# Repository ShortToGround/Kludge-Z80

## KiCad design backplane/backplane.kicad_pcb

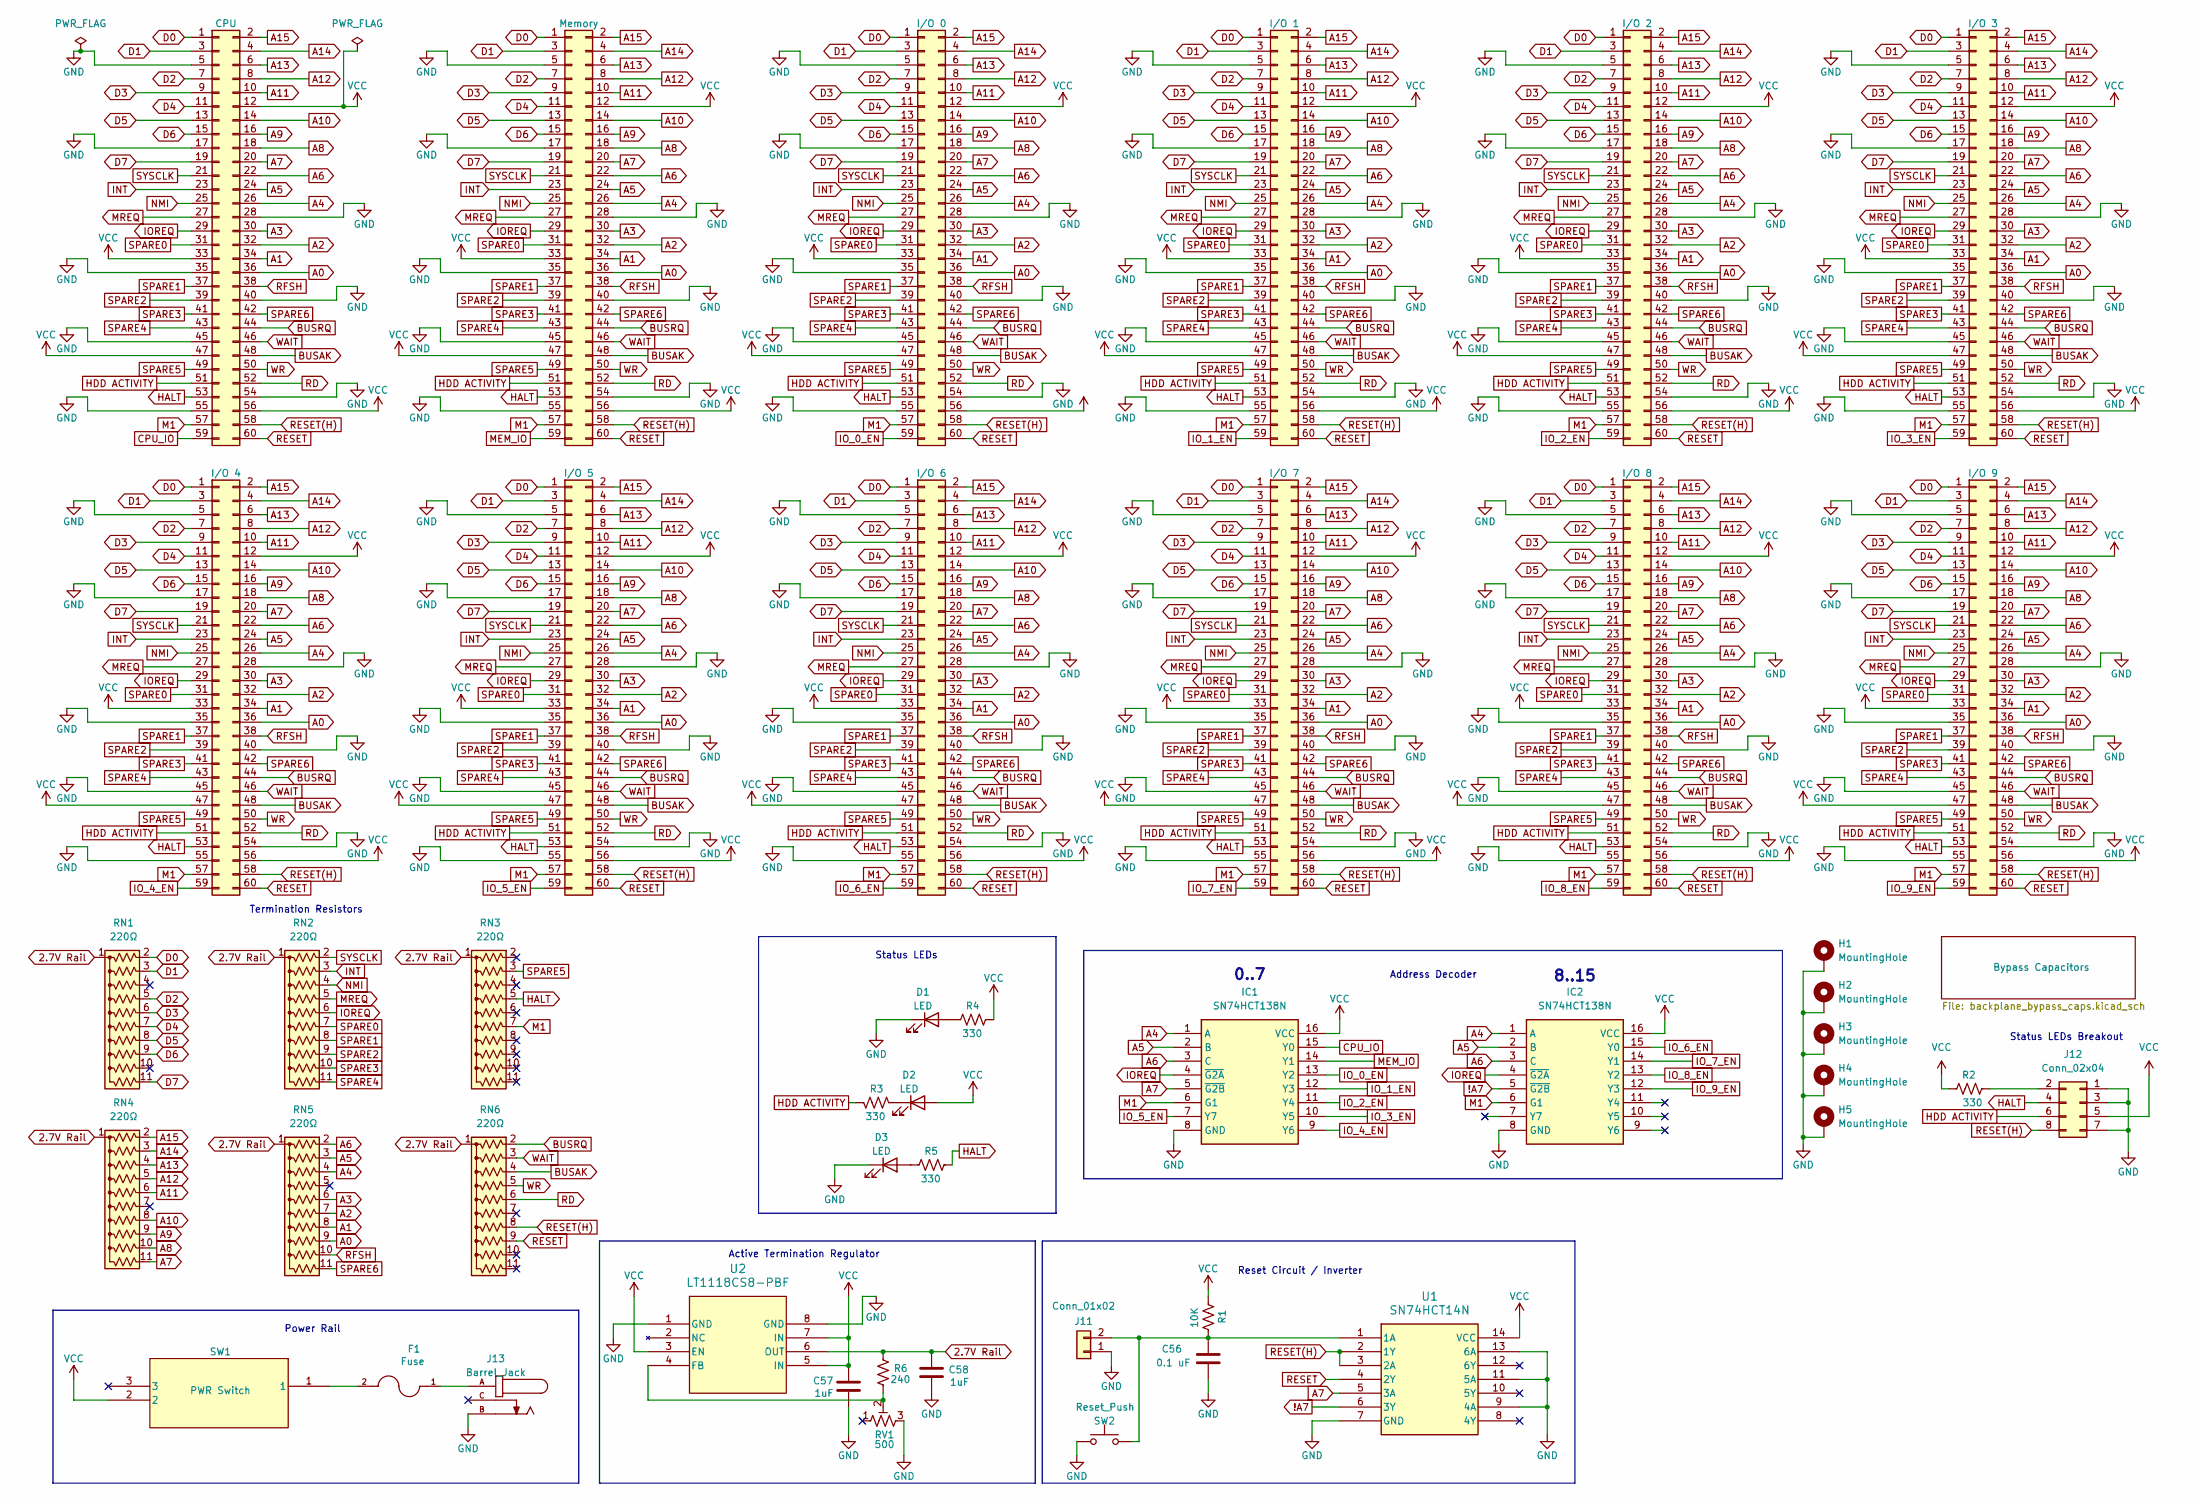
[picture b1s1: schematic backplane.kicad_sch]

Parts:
C56: 0.1 uF; C_Disc_D3.0mm_W1.6mm_P2.50mm
C57, C58: 1uF; C_Disc_D3.0mm_W1.6mm_P2.50mm
D1, D2, D3: LED; LED_D3.0mm
F1: Fuse; FUSE_4628
H1, H2, H3, H4, H5: MountingHole; MountingHole_3.2mm_M3_DIN965_Pad
IC1, IC2: SN74HCT138N; DIP-16_W7.62mm_Socket; Mouser Part Number 595-SN74HCT138N
J1: CPU; PinSocket_2x30_P2.54mm_Vertical
J2: Memory; PinSocket_2x30_P2.54mm_Vertical
J3: I/O 0; PinSocket_2x30_P2.54mm_Vertical
J4: I/O 1; PinSocket_2x30_P2.54mm_Vertical
J5: I/O 2; PinSocket_2x30_P2.54mm_Vertical
J6: I/O 3; PinSocket_2x30_P2.54mm_Vertical
J7: I/O 4; PinSocket_2x30_P2.54mm_Vertical
J8: I/O 5; PinSocket_2x30_P2.54mm_Vertical
J9: I/O 6; PinSocket_2x30_P2.54mm_Vertical
J10: I/O 7; PinSocket_2x30_P2.54mm_Vertical
J11: Conn_01x02; PinHeader_1x02_P2.54mm_Vertical
J12: Conn_02x04; PinHeader_2x04_P2.54mm_Vertical
J13: Barrel_Jack; TENSILITY_54-00129; PARTREV A
J15: I/O 8; PinSocket_2x30_P2.54mm_Vertical
J16: I/O 9; PinSocket_2x30_P2.54mm_Vertical
R1: 10K; R_Axial_DIN0207_L6.3mm_D2.5mm_P10.16mm_Horizontal
R2, R3, R4, R5: 330; R_Axial_DIN0207_L6.3mm_D2.5mm_P10.16mm_Horizontal
R6: 240; R_Axial_DIN0207_L6.3mm_D2.5mm_P10.16mm_Horizontal
RN1, RN2, RN3, RN4, RN5, RN6: 220Ω; R_Array_SIP11
RV1: 500; Potentiometer_Trim_06TR4DA103CP
SW1: PWR Switch; GH36P010001_APM
SW2: Reset_Push; SW_PUSH_6mm
U1: SN74HCT14N; DIP-14_W7.62mm_Socket
U2: LT1118CS8-PBF; LT1118-SO-8_S_LIT

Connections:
2.7V Rail: C58.1, R6.2, RN1.1 (common), RN2.1 (common), RN3.1 (common), RN4.1 (common), RN5.1 (common), RN6.1 (common), U2.6 (OUT)
!A7: IC2.5 (~G2B), U1.6 (3Y)
A0: J1.36, J2.36, J3.36, J4.36, J5.36, J6.36, J7.36, J8.36, J9.36, J10.36, J15.36, J16.36, RN5.9 (R8)
A1: J1.34, J2.34, J3.34, J4.34, J5.34, J6.34, J7.34, J8.34, J9.34, J10.34, J15.34, J16.34, RN5.8 (R7)
A2: J1.32, J2.32, J3.32, J4.32, J5.32, J6.32, J7.32, J8.32, J9.32, J10.32, J15.32, J16.32, RN5.7 (R6)
A3: J1.30, J2.30, J3.30, J4.30, J5.30, J6.30, J7.30, J8.30, J9.30, J10.30, J15.30, J16.30, RN5.6 (R5)
A4: IC1.1 (A), IC2.1 (A), J1.26, J2.26, J3.26, J4.26, J5.26, J6.26, J7.26, J8.26, J9.26, J10.26, J15.26, J16.26, RN5.4 (R3)
A5: IC1.2 (B), IC2.2 (B), J1.24, J2.24, J3.24, J4.24, J5.24, J6.24, J7.24, J8.24, J9.24, J10.24, J15.24, J16.24, RN5.3 (R2)
A6: IC1.3 (C), IC2.3 (C), J1.22, J2.22, J3.22, J4.22, J5.22, J6.22, J7.22, J8.22, J9.22, J10.22, J15.22, J16.22, RN5.2 (R1)
A7: IC1.5 (~G2B), J1.20, J2.20, J3.20, J4.20, J5.20, J6.20, J7.20, J8.20, J9.20, J10.20, J15.20, J16.20, RN4.11 (R10), U1.5 (3A)
A8: J1.18, J2.18, J3.18, J4.18, J5.18, J6.18, J7.18, J8.18, J9.18, J10.18, J15.18, J16.18, RN4.10 (R9)
A9: J1.16, J2.16, J3.16, J4.16, J5.16, J6.16, J7.16, J8.16, J9.16, J10.16, J15.16, J16.16, RN4.9 (R8)
A10: J1.14, J2.14, J3.14, J4.14, J5.14, J6.14, J7.14, J8.14, J9.14, J10.14, J15.14, J16.14, RN4.8 (R7)
A11: J1.10, J2.10, J3.10, J4.10, J5.10, J6.10, J7.10, J8.10, J9.10, J10.10, J15.10, J16.10, RN4.6 (R5)
A12: J1.8, J2.8, J3.8, J4.8, J5.8, J6.8, J7.8, J8.8, J9.8, J10.8, J15.8, J16.8, RN4.5 (R4)
A13: J1.6, J2.6, J3.6, J4.6, J5.6, J6.6, J7.6, J8.6, J9.6, J10.6, J15.6, J16.6, RN4.4 (R3)
A14: J1.4, J2.4, J3.4, J4.4, J5.4, J6.4, J7.4, J8.4, J9.4, J10.4, J15.4, J16.4, RN4.3 (R2)
A15: J1.2, J2.2, J3.2, J4.2, J5.2, J6.2, J7.2, J8.2, J9.2, J10.2, J15.2, J16.2, RN4.2 (R1)
BUSAK: J1.48, J2.48, J3.48, J4.48, J5.48, J6.48, J7.48, J8.48, J9.48, J10.48, J15.48, J16.48, RN6.4 (R3)
BUSRQ: J1.44, J2.44, J3.44, J4.44, J5.44, J6.44, J7.44, J8.44, J9.44, J10.44, J15.44, J16.44, RN6.2 (R1)
CPU_IO: IC1.15 (Y0), J1.59
D0: J1.1, J2.1, J3.1, J4.1, J5.1, J6.1, J7.1, J8.1, J9.1, J10.1, J15.1, J16.1, RN1.2 (R1)
D1: J1.3, J2.3, J3.3, J4.3, J5.3, J6.3, J7.3, J8.3, J9.3, J10.3, J15.3, J16.3, RN1.3 (R2)
D2: J1.7, J2.7, J3.7, J4.7, J5.7, J6.7, J7.7, J8.7, J9.7, J10.7, J15.7, J16.7, RN1.5 (R4)
D3: J1.9, J2.9, J3.9, J4.9, J5.9, J6.9, J7.9, J8.9, J9.9, J10.9, J15.9, J16.9, RN1.6 (R5)
D4: J1.11, J2.11, J3.11, J4.11, J5.11, J6.11, J7.11, J8.11, J9.11, J10.11, J15.11, J16.11, RN1.7 (R6)
D5: J1.13, J2.13, J3.13, J4.13, J5.13, J6.13, J7.13, J8.13, J9.13, J10.13, J15.13, J16.13, RN1.8 (R7)
D6: J1.15, J2.15, J3.15, J4.15, J5.15, J6.15, J7.15, J8.15, J9.15, J10.15, J15.15, J16.15, RN1.9 (R8)
D7: J1.19, J2.19, J3.19, J4.19, J5.19, J6.19, J7.19, J8.19, J9.19, J10.19, J15.19, J16.19, RN1.11 (R10)
GND: C56.2, C57.2, C58.2, D1.1 (K), D3.1 (K), H1.1, H2.1, H3.1, H4.1, H5.1, IC1.8 (GND), IC2.8 (GND), J1.5, J1.17, J1.28, J1.35, J1.40, J1.45, J1.54, J1.55, J2.5, J2.17, J2.28, J2.35, J2.40, J2.45, J2.54, J2.55, J3.5, J3.17, J3.28, J3.35, J3.40, J3.45, J3.54, J3.55, J4.5, J4.17, J4.28, J4.35, J4.40, J4.45, J4.54, J4.55, J5.5, J5.17, J5.28, J5.35, J5.40, J5.45, J5.54, J5.55, J6.5, J6.17, J6.28, J6.35, J6.40, J6.45, J6.54, J6.55, J7.5, J7.17, J7.28, J7.35, J7.40, J7.45, J7.54, J7.55, J8.5, J8.17, J8.28, J8.35, J8.40, J8.45, J8.54, J8.55, J9.5, J9.17, J9.28, J9.35, J9.40, J9.45, J9.54, J9.55, J10.5, J10.17, J10.28, J10.35, J10.40, J10.45, J10.54, J10.55, J11.1, J12.1, J12.3, J12.7, J13.B, J15.5, J15.17, J15.28, J15.35, J15.40, J15.45, J15.54, J15.55, J16.5, J16.17, J16.28, J16.35, J16.40, J16.45, J16.54, J16.55, RV1.3, SW2.1, U1.7 (GND), U1.9 (4A), U1.11 (5A), U1.13 (6A), U2.1 (GND), U2.8 (GND); also elsewhere on the board
HALT: J1.53, J2.53, J3.53, J4.53, J5.53, J6.53, J7.53, J8.53, J9.53, J10.53, J12.4, J15.53, J16.53, R5.2, RN3.5 (R4)
HDD ACTIVITY: J1.51, J2.51, J3.51, J4.51, J5.51, J6.51, J7.51, J8.51, J9.51, J10.51, J12.6, J15.51, J16.51, R3.2
INT: J1.23, J2.23, J3.23, J4.23, J5.23, J6.23, J7.23, J8.23, J9.23, J10.23, J15.23, J16.23, RN2.3 (R2)
IOREQ: IC1.4 (~G2A), IC2.4 (~G2A), J1.29, J2.29, J3.29, J4.29, J5.29, J6.29, J7.29, J8.29, J9.29, J10.29, J15.29, J16.29, RN2.6 (R5)
IO_0_EN: IC1.13 (Y2), J3.59
IO_1_EN: IC1.12 (Y3), J4.59
IO_2_EN: IC1.11 (Y4), J5.59
IO_3_EN: IC1.10 (Y5), J6.59
IO_4_EN: IC1.9 (Y6), J7.59
IO_5_EN: IC1.7 (Y7), J8.59
IO_6_EN: IC2.15 (Y0), J9.59
IO_7_EN: IC2.14 (Y1), J10.59
IO_8_EN: IC2.13 (Y2), J15.59
IO_9_EN: IC2.12 (Y3), J16.59
M1: IC1.6 (G1), IC2.6 (G1), J1.57, J2.57, J3.57, J4.57, J5.57, J6.57, J7.57, J8.57, J9.57, J10.57, J15.57, J16.57, RN3.7 (R6)
MEM_IO: IC1.14 (Y1), J2.59
MREQ: J1.27, J2.27, J3.27, J4.27, J5.27, J6.27, J7.27, J8.27, J9.27, J10.27, J15.27, J16.27, RN2.5 (R4)
NMI: J1.25, J2.25, J3.25, J4.25, J5.25, J6.25, J7.25, J8.25, J9.25, J10.25, J15.25, J16.25, RN2.4 (R3)
unnamed: D1.2 (A), R4.1
unnamed: D2.1 (K), R3.1
unnamed: D3.2 (A), R5.1
unnamed: F1.1, J13.A
unnamed: F1.2, SW1.1
unnamed: C56.1, J11.2, R1.2, SW2.2, U1.1 (1A)
unnamed: J12.2, R2.2
unnamed: R6.1, RV1.2, U2.4 (FB)
RD: J1.52, J2.52, J3.52, J4.52, J5.52, J6.52, J7.52, J8.52, J9.52, J10.52, J15.52, J16.52, RN6.6 (R5)
RESET: J1.60, J2.60, J3.60, J4.60, J5.60, J6.60, J7.60, J8.60, J9.60, J10.60, J15.60, J16.60, RN6.9 (R8), U1.4 (2Y)
RESET(H): J1.58, J2.58, J3.58, J4.58, J5.58, J6.58, J7.58, J8.58, J9.58, J10.58, J12.8, J15.58, J16.58, RN6.8 (R7), U1.2 (1Y), U1.3 (2A)
RFSH: J1.38, J2.38, J3.38, J4.38, J5.38, J6.38, J7.38, J8.38, J9.38, J10.38, J15.38, J16.38, RN5.10 (R9)
SPARE0: J1.31, J2.31, J3.31, J4.31, J5.31, J6.31, J7.31, J8.31, J9.31, J10.31, J15.31, J16.31, RN2.7 (R6)
SPARE1: J1.37, J2.37, J3.37, J4.37, J5.37, J6.37, J7.37, J8.37, J9.37, J10.37, J15.37, J16.37, RN2.8 (R7)
SPARE2: J1.39, J2.39, J3.39, J4.39, J5.39, J6.39, J7.39, J8.39, J9.39, J10.39, J15.39, J16.39, RN2.9 (R8)
SPARE3: J1.41, J2.41, J3.41, J4.41, J5.41, J6.41, J7.41, J8.41, J9.41, J10.41, J15.41, J16.41, RN2.10 (R9)
SPARE4: J1.43, J2.43, J3.43, J4.43, J5.43, J6.43, J7.43, J8.43, J9.43, J10.43, J15.43, J16.43, RN2.11 (R10)
SPARE5: J1.49, J2.49, J3.49, J4.49, J5.49, J6.49, J7.49, J8.49, J9.49, J10.49, J15.49, J16.49, RN3.3 (R2)
SPARE6: J1.42, J2.42, J3.42, J4.42, J5.42, J6.42, J7.42, J8.42, J9.42, J10.42, J15.42, J16.42, RN5.11 (R10)
SYSCLK: J1.21, J2.21, J3.21, J4.21, J5.21, J6.21, J7.21, J8.21, J9.21, J10.21, J15.21, J16.21, RN2.2 (R1)
VCC: C57.1, D2.2 (A), IC1.16 (VCC), IC2.16 (VCC), J1.12, J1.33, J1.47, J1.56, J2.12, J2.33, J2.47, J2.56, J3.12, J3.33, J3.47, J3.56, J4.12, J4.33, J4.47, J4.56, J5.12, J5.33, J5.47, J5.56, J6.12, J6.33, J6.47, J6.56, J7.12, J7.33, J7.47, J7.56, J8.12, J8.33, J8.47, J8.56, J9.12, J9.33, J9.47, J9.56, J10.12, J10.33, J10.47, J10.56, J12.5, J15.12, J15.33, J15.47, J15.56, J16.12, J16.33, J16.47, J16.56, R1.1, R2.1, R4.2, SW1.2, U1.14 (VCC), U2.3 (EN), U2.5 (IN), U2.7 (IN); also elsewhere on the board
WAIT: J1.46, J2.46, J3.46, J4.46, J5.46, J6.46, J7.46, J8.46, J9.46, J10.46, J15.46, J16.46, RN6.3 (R2)
WR: J1.50, J2.50, J3.50, J4.50, J5.50, J6.50, J7.50, J8.50, J9.50, J10.50, J15.50, J16.50, RN6.5 (R4)

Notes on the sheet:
Address Decoder
Status LEDs
Termination Resistors
Active Termination Regulator
Power Rail
Status LEDs Breakout
8..15
Reset Circuit / Inverter
0..7

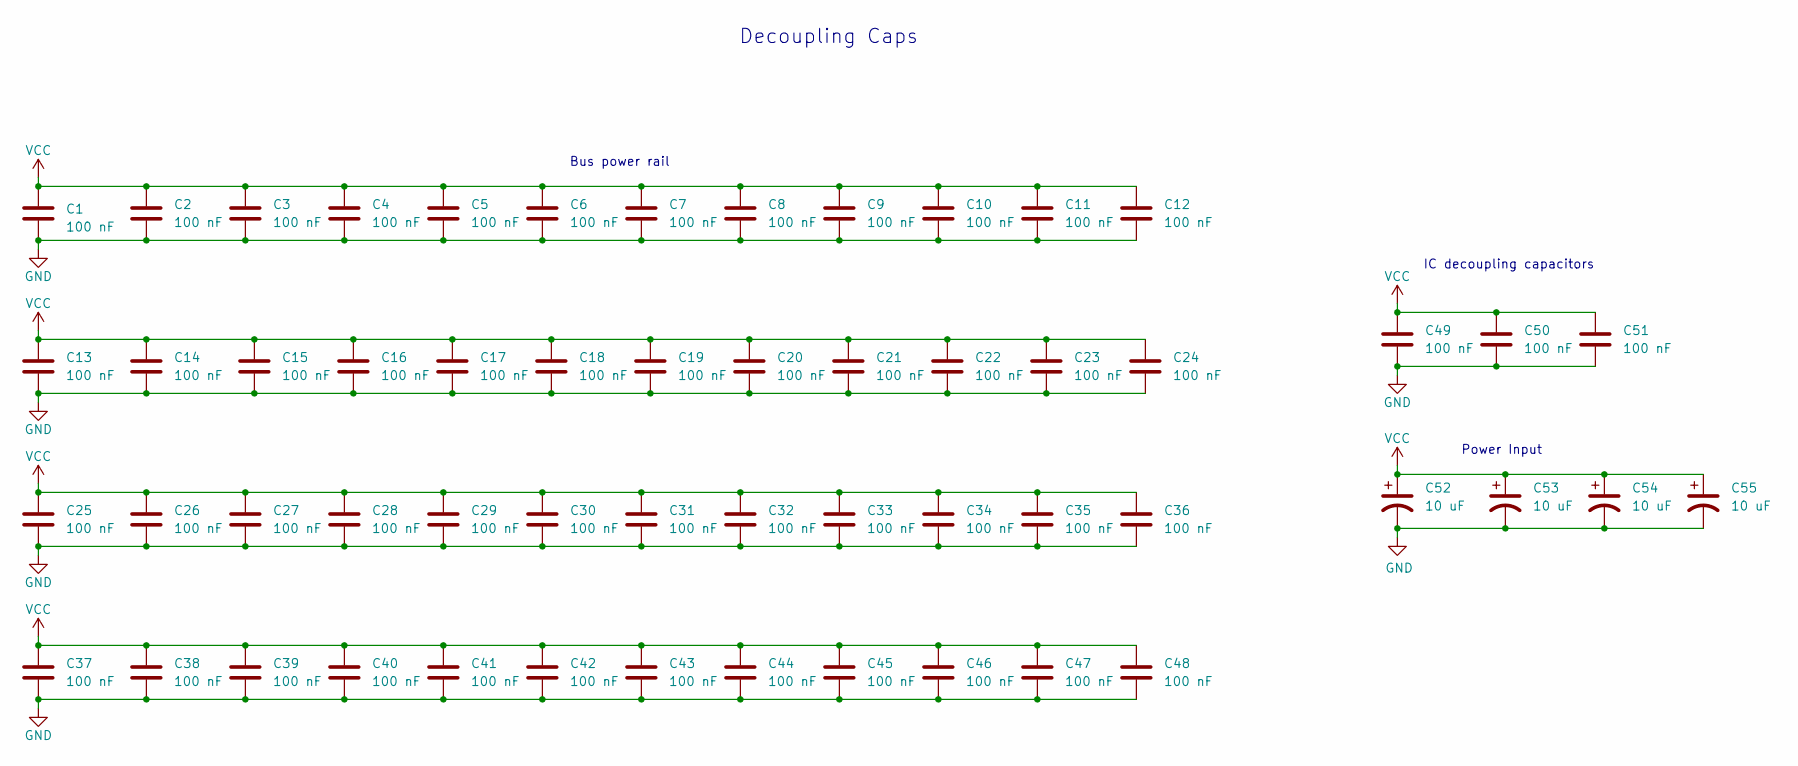
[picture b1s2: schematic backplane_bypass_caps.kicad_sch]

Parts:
C1, C2, C3, C4, C5, C6, C7, C8, C9, C10, C11, C12, C13, C14, C15, C16, C17, C18, C19, C20, C21, C22, C23, C24, C25, C26, C27, C28, C29, C30, C31, C32, C33, C34, C35, C36, C37, C38, C39, C40, C41, C42, C43, C44, C45, C46, C47, C48, C49, C50, C51: 100 nF; C_Disc_D3.0mm_W1.6mm_P2.50mm
C52, C53, C54, C55: 10 uF; C_Radial_D6.3mm_H7.0mm_P2.50mm

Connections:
GND: C1.2, C2.2, C3.2, C4.2, C5.2, C6.2, C7.2, C8.2, C9.2, C10.2, C11.2, C12.2, C13.2, C14.2, C15.2, C16.2, C17.2, C18.2, C19.2, C20.2, C21.2, C22.2, C23.2, C24.2, C25.2, C26.2, C27.2, C28.2, C29.2, C30.2, C31.2, C32.2, C33.2, C34.2, C35.2, C36.2, C37.2, C38.2, C39.2, C40.2, C41.2, C42.2, C43.2, C44.2, C45.2, C46.2, C47.2, C48.2, C49.2, C50.2, C51.2, C52.2, C53.2, C54.2, C55.2; also elsewhere on the board
VCC: C1.1, C2.1, C3.1, C4.1, C5.1, C6.1, C7.1, C8.1, C9.1, C10.1, C11.1, C12.1, C13.1, C14.1, C15.1, C16.1, C17.1, C18.1, C19.1, C20.1, C21.1, C22.1, C23.1, C24.1, C25.1, C26.1, C27.1, C28.1, C29.1, C30.1, C31.1, C32.1, C33.1, C34.1, C35.1, C36.1, C37.1, C38.1, C39.1, C40.1, C41.1, C42.1, C43.1, C44.1, C45.1, C46.1, C47.1, C48.1, C49.1, C50.1, C51.1, C52.1, C53.1, C54.1, C55.1; also elsewhere on the board

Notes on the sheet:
Power Input
IC decoupling capacitors
Bus power rail
Decoupling Caps

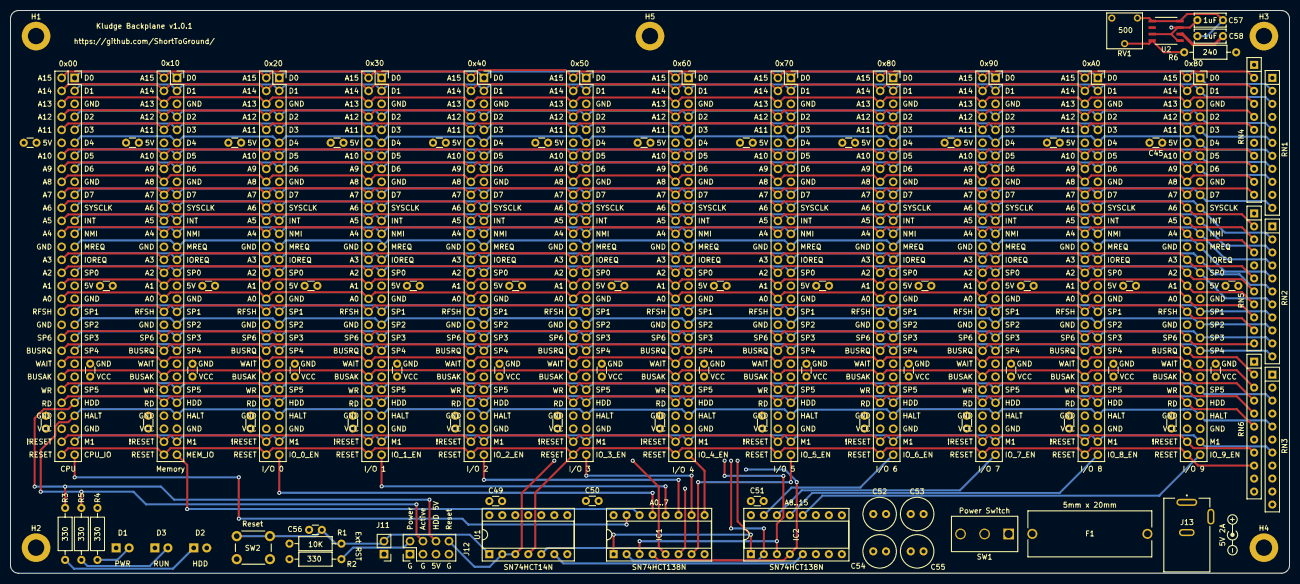
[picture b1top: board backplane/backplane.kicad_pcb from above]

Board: 4 copper layers, 250.0 x 110.0 mm, 101 parts (0 on the bottom side), 71 nets.

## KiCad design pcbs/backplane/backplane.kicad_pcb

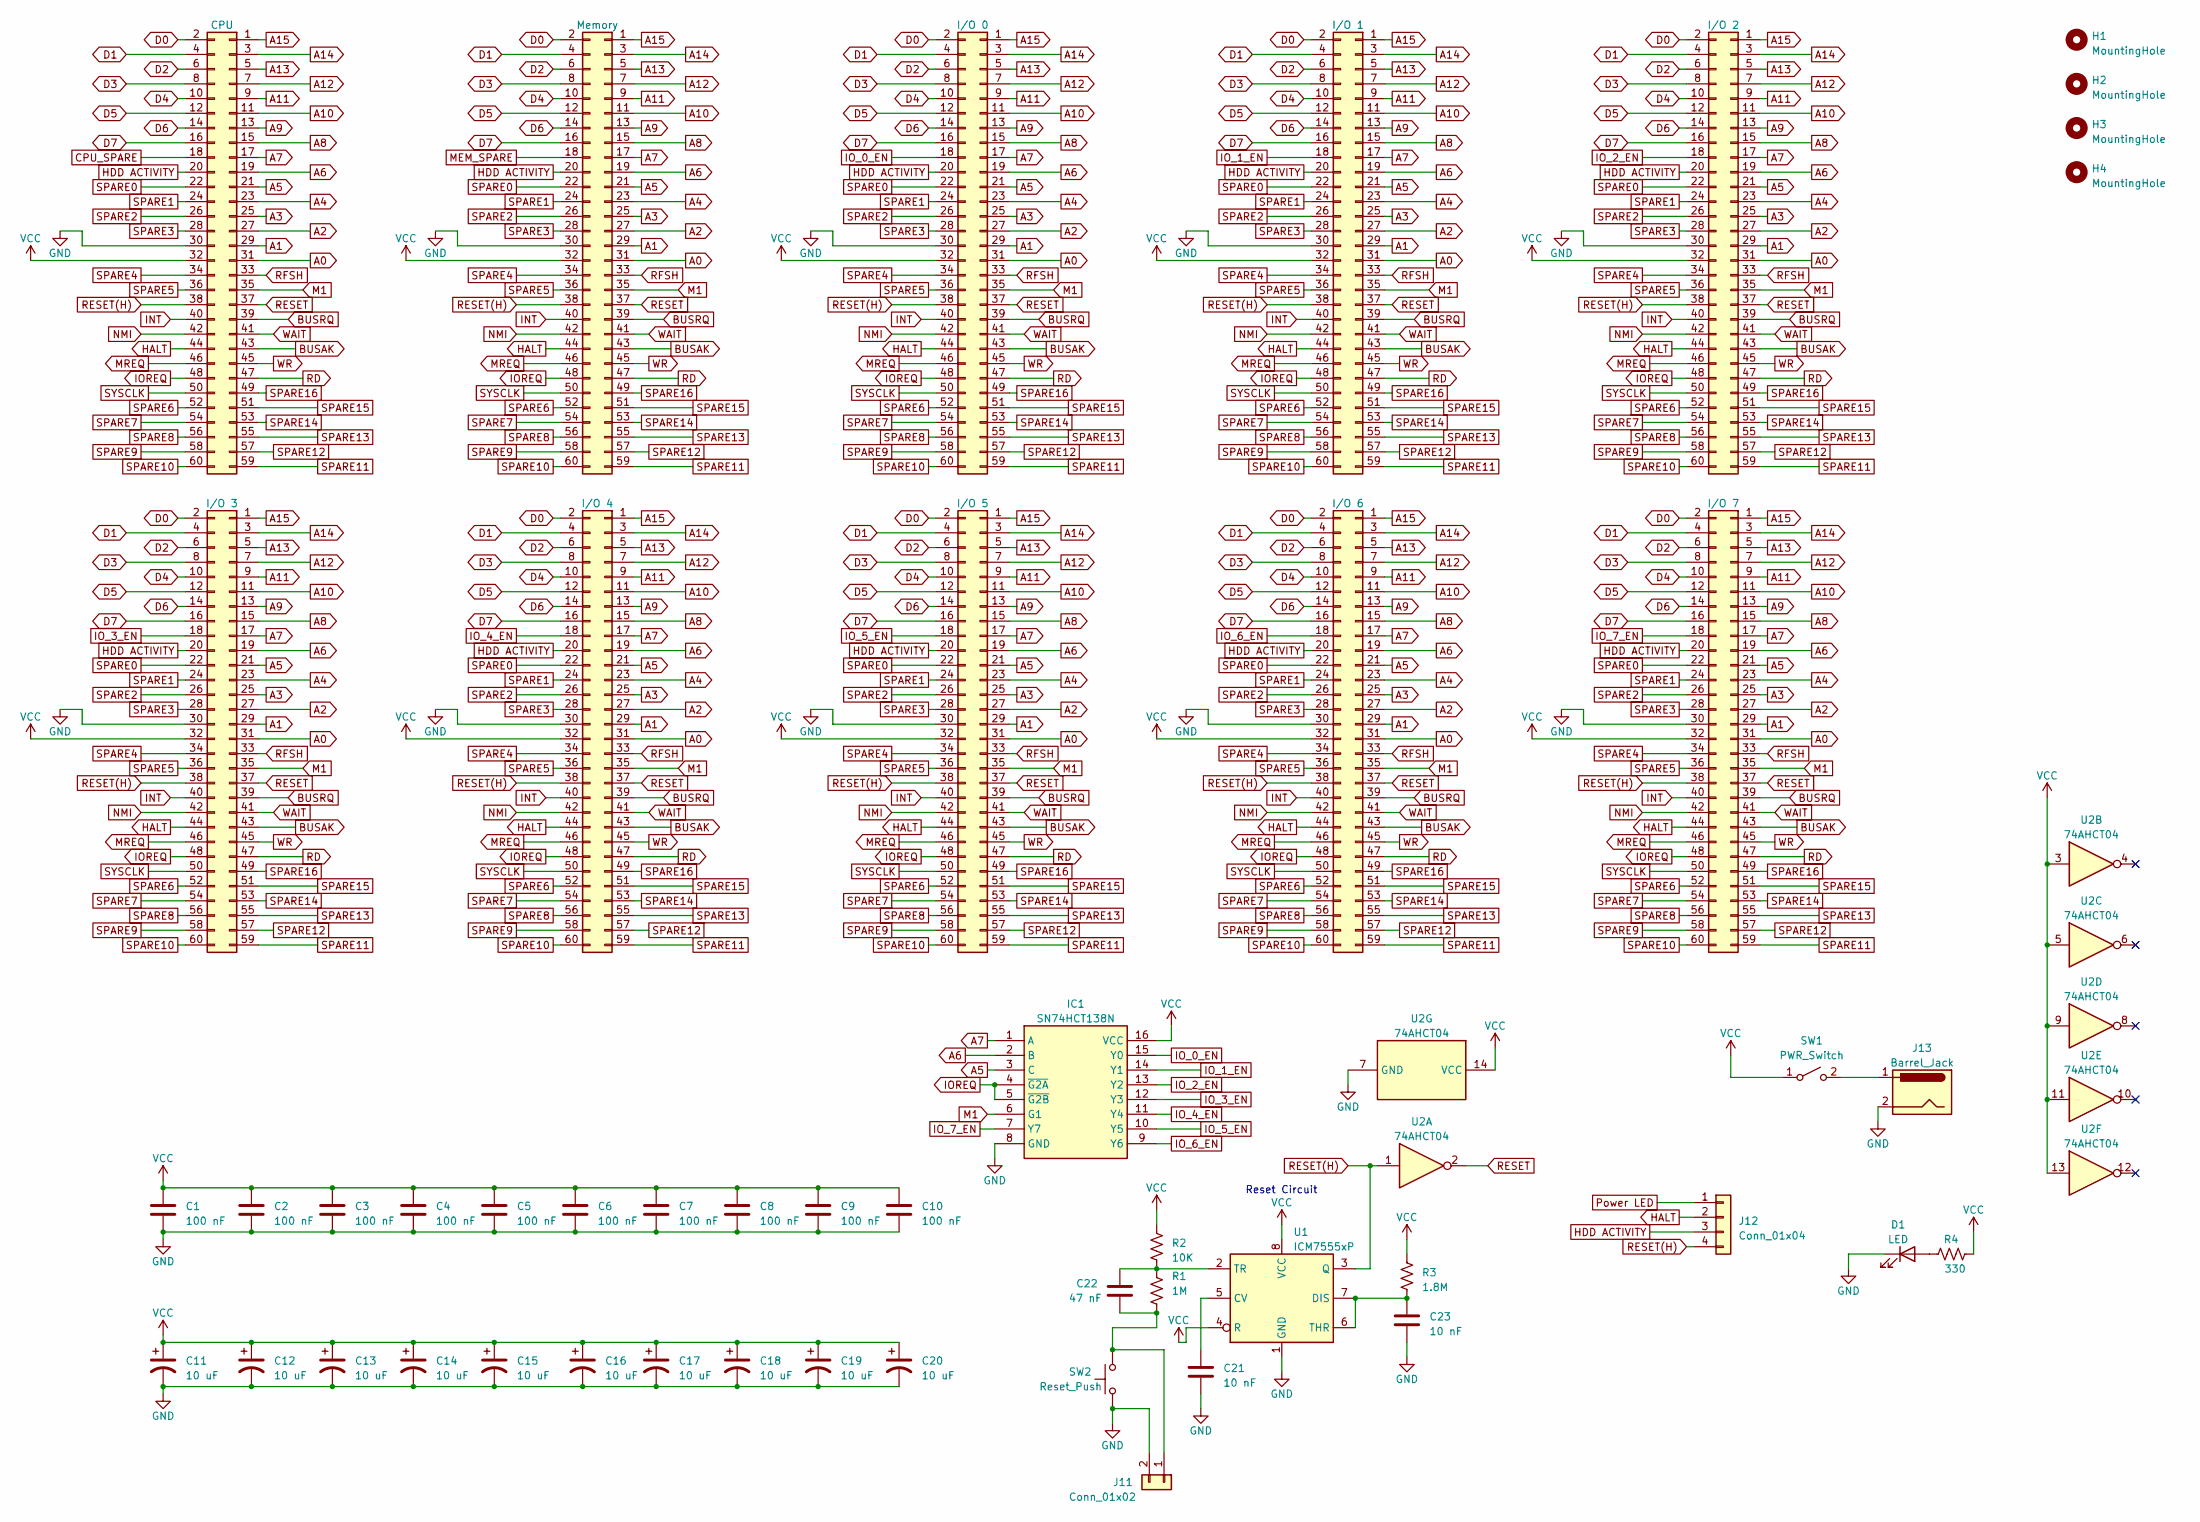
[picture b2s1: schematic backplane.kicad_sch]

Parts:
C1, C2, C3, C4, C5, C6, C7, C8, C9, C10: 100 nF; C_Disc_D3.0mm_W1.6mm_P2.50mm
C11, C12, C13, C14, C15, C16, C17, C18, C19, C20: 10 uF; C_Radial_D6.3mm_H7.0mm_P2.50mm
C21, C23: 10 nF; C_Disc_D3.0mm_W1.6mm_P2.50mm
C22: 47 nF; C_Disc_D3.0mm_W1.6mm_P2.50mm
D1: LED; LED_D3.0mm
H1, H2, H3, H4: MountingHole; MountingHole_3.2mm_M3
IC1: SN74HCT138N; Mouser Part Number 595-SN74HCT138N
J1: CPU; PinSocket_2x30_P2.54mm_Vertical
J2: Memory; PinSocket_2x30_P2.54mm_Vertical
J3: I/O 0; PinSocket_2x30_P2.54mm_Vertical
J4: I/O 1; PinSocket_2x30_P2.54mm_Vertical
J5: I/O 2; PinSocket_2x30_P2.54mm_Vertical
J6: I/O 3; PinSocket_2x30_P2.54mm_Vertical
J7: I/O 4; PinSocket_2x30_P2.54mm_Vertical
J8: I/O 5; PinSocket_2x30_P2.54mm_Vertical
J9: I/O 6; PinSocket_2x30_P2.54mm_Vertical
J10: I/O 7; PinSocket_2x30_P2.54mm_Vertical
J11: Conn_01x02; PinHeader_1x02_P2.54mm_Vertical
J12: Conn_01x04; PinHeader_1x04_P2.54mm_Vertical
J13: Barrel_Jack; BarrelJack_Horizontal
R1: 1M; R_Axial_DIN0204_L3.6mm_D1.6mm_P5.08mm_Horizontal
R2: 10K; R_Axial_DIN0204_L3.6mm_D1.6mm_P5.08mm_Horizontal
R3: 1.8M; R_Axial_DIN0204_L3.6mm_D1.6mm_P5.08mm_Horizontal
R4: 330; R_Axial_DIN0204_L3.6mm_D1.6mm_P5.08mm_Horizontal
SW1: PWR_Switch; SW_DIP_SPSTx01_Slide_9.78x4.72mm_W7.62mm_P2.54mm
SW2: Reset_Push; SW_PUSH_6mm
U1: ICM7555xP; DIP-8_W7.62mm
U2: 74AHCT04; DIP-14_W7.62mm

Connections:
A0: J1.31, J2.31, J3.31, J4.31, J5.31, J6.31, J7.31, J8.31, J9.31, J10.31
A1: J1.29, J2.29, J3.29, J4.29, J5.29, J6.29, J7.29, J8.29, J9.29, J10.29
A2: J1.27, J2.27, J3.27, J4.27, J5.27, J6.27, J7.27, J8.27, J9.27, J10.27
A3: J1.25, J2.25, J3.25, J4.25, J5.25, J6.25, J7.25, J8.25, J9.25, J10.25
A4: J1.23, J2.23, J3.23, J4.23, J5.23, J6.23, J7.23, J8.23, J9.23, J10.23
A5: IC1.3 (C), J1.21, J2.21, J3.21, J4.21, J5.21, J6.21, J7.21, J8.21, J9.21, J10.21
A6: IC1.2 (B), J1.19, J2.19, J3.19, J4.19, J5.19, J6.19, J7.19, J8.19, J9.19, J10.19
A7: IC1.1 (A), J1.17, J2.17, J3.17, J4.17, J5.17, J6.17, J7.17, J8.17, J9.17, J10.17
A8: J1.15, J2.15, J3.15, J4.15, J5.15, J6.15, J7.15, J8.15, J9.15, J10.15
A9: J1.13, J2.13, J3.13, J4.13, J5.13, J6.13, J7.13, J8.13, J9.13, J10.13
A10: J1.11, J2.11, J3.11, J4.11, J5.11, J6.11, J7.11, J8.11, J9.11, J10.11
A11: J1.9, J2.9, J3.9, J4.9, J5.9, J6.9, J7.9, J8.9, J9.9, J10.9
A12: J1.7, J2.7, J3.7, J4.7, J5.7, J6.7, J7.7, J8.7, J9.7, J10.7
A13: J1.5, J2.5, J3.5, J4.5, J5.5, J6.5, J7.5, J8.5, J9.5, J10.5
A14: J1.3, J2.3, J3.3, J4.3, J5.3, J6.3, J7.3, J8.3, J9.3, J10.3
A15: J1.1, J2.1, J3.1, J4.1, J5.1, J6.1, J7.1, J8.1, J9.1, J10.1
BUSAK: J1.43, J2.43, J3.43, J4.43, J5.43, J6.43, J7.43, J8.43, J9.43, J10.43
BUSRQ: J1.39, J2.39, J3.39, J4.39, J5.39, J6.39, J7.39, J8.39, J9.39, J10.39
CPU_SPARE: J1.18
D0: J1.2, J2.2, J3.2, J4.2, J5.2, J6.2, J7.2, J8.2, J9.2, J10.2
D1: J1.4, J2.4, J3.4, J4.4, J5.4, J6.4, J7.4, J8.4, J9.4, J10.4
D2: J1.6, J2.6, J3.6, J4.6, J5.6, J6.6, J7.6, J8.6, J9.6, J10.6
D3: J1.8, J2.8, J3.8, J4.8, J5.8, J6.8, J7.8, J8.8, J9.8, J10.8
D4: J1.10, J2.10, J3.10, J4.10, J5.10, J6.10, J7.10, J8.10, J9.10, J10.10
D5: J1.12, J2.12, J3.12, J4.12, J5.12, J6.12, J7.12, J8.12, J9.12, J10.12
D6: J1.14, J2.14, J3.14, J4.14, J5.14, J6.14, J7.14, J8.14, J9.14, J10.14
D7: J1.16, J2.16, J3.16, J4.16, J5.16, J6.16, J7.16, J8.16, J9.16, J10.16
GND: C1.2, C2.2, C3.2, C4.2, C5.2, C6.2, C7.2, C8.2, C9.2, C10.2, C11.2, C12.2, C13.2, C14.2, C15.2, C16.2, C17.2, C18.2, C19.2, C20.2, C21.2, C23.2, D1.1 (K), IC1.8 (GND), J1.30, J2.30, J3.30, J4.30, J5.30, J6.30, J7.30, J8.30, J9.30, J10.30, J11.2, J13.2, SW2.1, U1.1 (GND), U2.7 (GND)
HALT: J1.44, J2.44, J3.44, J4.44, J5.44, J6.44, J7.44, J8.44, J9.44, J10.44, J12.2
HDD ACTIVITY: J1.20, J2.20, J3.20, J4.20, J5.20, J6.20, J7.20, J8.20, J9.20, J10.20, J12.3
INT: J1.40, J2.40, J3.40, J4.40, J5.40, J6.40, J7.40, J8.40, J9.40, J10.40
IOREQ: IC1.4 (~G2A), IC1.5 (~G2B), J1.48, J2.48, J3.48, J4.48, J5.48, J6.48, J7.48, J8.48, J9.48, J10.48
IO_0_EN: IC1.15 (Y0), J3.18
IO_1_EN: IC1.14 (Y1), J4.18
IO_2_EN: IC1.13 (Y2), J5.18
IO_3_EN: IC1.12 (Y3), J6.18
IO_4_EN: IC1.11 (Y4), J7.18
IO_5_EN: IC1.10 (Y5), J8.18
IO_6_EN: IC1.9 (Y6), J9.18
IO_7_EN: IC1.7 (Y7), J10.18
M1: IC1.6 (G1), J1.35, J2.35, J3.35, J4.35, J5.35, J6.35, J7.35, J8.35, J9.35, J10.35
MEM_SPARE: J2.18
MREQ: J1.46, J2.46, J3.46, J4.46, J5.46, J6.46, J7.46, J8.46, J9.46, J10.46
NMI: J1.42, J2.42, J3.42, J4.42, J5.42, J6.42, J7.42, J8.42, J9.42, J10.42
unnamed: D1.2 (A), R4.1
unnamed: C22.2, J11.1, R1.2, SW2.2
unnamed: J13.1, SW1.2 (B)
unnamed: C21.1, U1.5 (CV)
unnamed: C23.1, R3.2, U1.6 (THR), U1.7 (DIS)
unnamed: C22.1, R1.1, R2.2, U1.2 (TR)
Power LED: J12.1
RD: J1.47, J2.47, J3.47, J4.47, J5.47, J6.47, J7.47, J8.47, J9.47, J10.47
RESET: J1.37, J2.37, J3.37, J4.37, J5.37, J6.37, J7.37, J8.37, J9.37, J10.37, U2.2
RESET(H): J1.38, J2.38, J3.38, J4.38, J5.38, J6.38, J7.38, J8.38, J9.38, J10.38, J12.4, U1.3 (Q), U2.1
RFSH: J1.33, J2.33, J3.33, J4.33, J5.33, J6.33, J7.33, J8.33, J9.33, J10.33
SPARE0: J1.22, J2.22, J3.22, J4.22, J5.22, J6.22, J7.22, J8.22, J9.22, J10.22
SPARE1: J1.24, J2.24, J3.24, J4.24, J5.24, J6.24, J7.24, J8.24, J9.24, J10.24
SPARE2: J1.26, J2.26, J3.26, J4.26, J5.26, J6.26, J7.26, J8.26, J9.26, J10.26
SPARE3: J1.28, J2.28, J3.28, J4.28, J5.28, J6.28, J7.28, J8.28, J9.28, J10.28
SPARE4: J1.34, J2.34, J3.34, J4.34, J5.34, J6.34, J7.34, J8.34, J9.34, J10.34
SPARE5: J1.36, J2.36, J3.36, J4.36, J5.36, J6.36, J7.36, J8.36, J9.36, J10.36
SPARE6: J1.52, J2.52, J3.52, J4.52, J5.52, J6.52, J7.52, J8.52, J9.52, J10.52
SPARE7: J1.54, J2.54, J3.54, J4.54, J5.54, J6.54, J7.54, J8.54, J9.54, J10.54
SPARE8: J1.56, J2.56, J3.56, J4.56, J5.56, J6.56, J7.56, J8.56, J9.56, J10.56
SPARE9: J1.58, J2.58, J3.58, J4.58, J5.58, J6.58, J7.58, J8.58, J9.58, J10.58
SPARE10: J1.60, J2.60, J3.60, J4.60, J5.60, J6.60, J7.60, J8.60, J9.60, J10.60
SPARE11: J1.59, J2.59, J3.59, J4.59, J5.59, J6.59, J7.59, J8.59, J9.59, J10.59
SPARE12: J1.57, J2.57, J3.57, J4.57, J5.57, J6.57, J7.57, J8.57, J9.57, J10.57
SPARE13: J1.55, J2.55, J3.55, J4.55, J5.55, J6.55, J7.55, J8.55, J9.55, J10.55
SPARE14: J1.53, J2.53, J3.53, J4.53, J5.53, J6.53, J7.53, J8.53, J9.53, J10.53
SPARE15: J1.51, J2.51, J3.51, J4.51, J5.51, J6.51, J7.51, J8.51, J9.51, J10.51
SPARE16: J1.49, J2.49, J3.49, J4.49, J5.49, J6.49, J7.49, J8.49, J9.49, J10.49
SYSCLK: J1.50, J2.50, J3.50, J4.50, J5.50, J6.50, J7.50, J8.50, J9.50, J10.50
VCC: C1.1, C2.1, C3.1, C4.1, C5.1, C6.1, C7.1, C8.1, C9.1, C10.1, C11.1, C12.1, C13.1, C14.1, C15.1, C16.1, C17.1, C18.1, C19.1, C20.1, IC1.16 (VCC), J1.32, J2.32, J3.32, J4.32, J5.32, J6.32, J7.32, J8.32, J9.32, J10.32, R2.1, R3.1, R4.2, SW1.1 (A), U1.4 (R), U1.8 (VCC), U2.3, U2.5, U2.9, U2.11, U2.13, U2.14 (VCC)
WAIT: J1.41, J2.41, J3.41, J4.41, J5.41, J6.41, J7.41, J8.41, J9.41, J10.41
WR: J1.45, J2.45, J3.45, J4.45, J5.45, J6.45, J7.45, J8.45, J9.45, J10.45

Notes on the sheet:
Reset Circuit

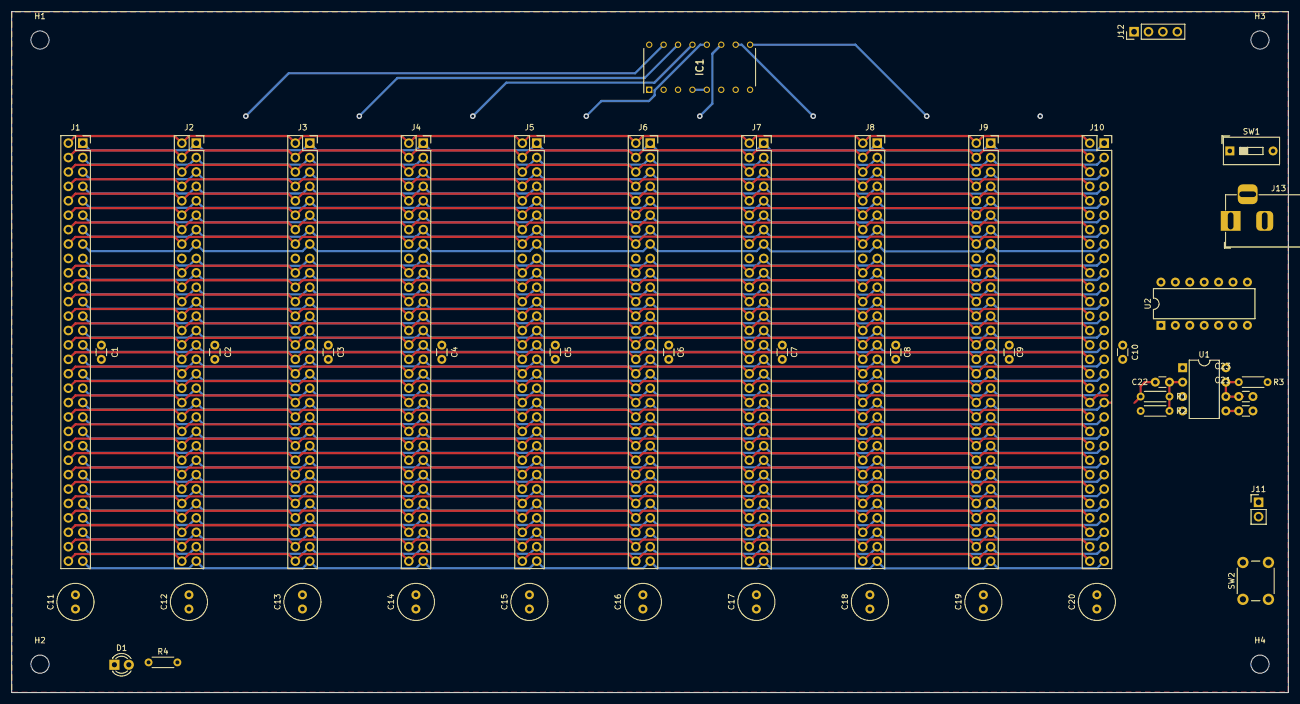
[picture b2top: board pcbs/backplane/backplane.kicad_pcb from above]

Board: 4 copper layers, 225.0 x 120.0 mm, 50 parts (0 on the bottom side), 73 nets.
